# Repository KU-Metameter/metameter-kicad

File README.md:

Bluetooth Multimeter Senior Design Project  
Contains KiCad files

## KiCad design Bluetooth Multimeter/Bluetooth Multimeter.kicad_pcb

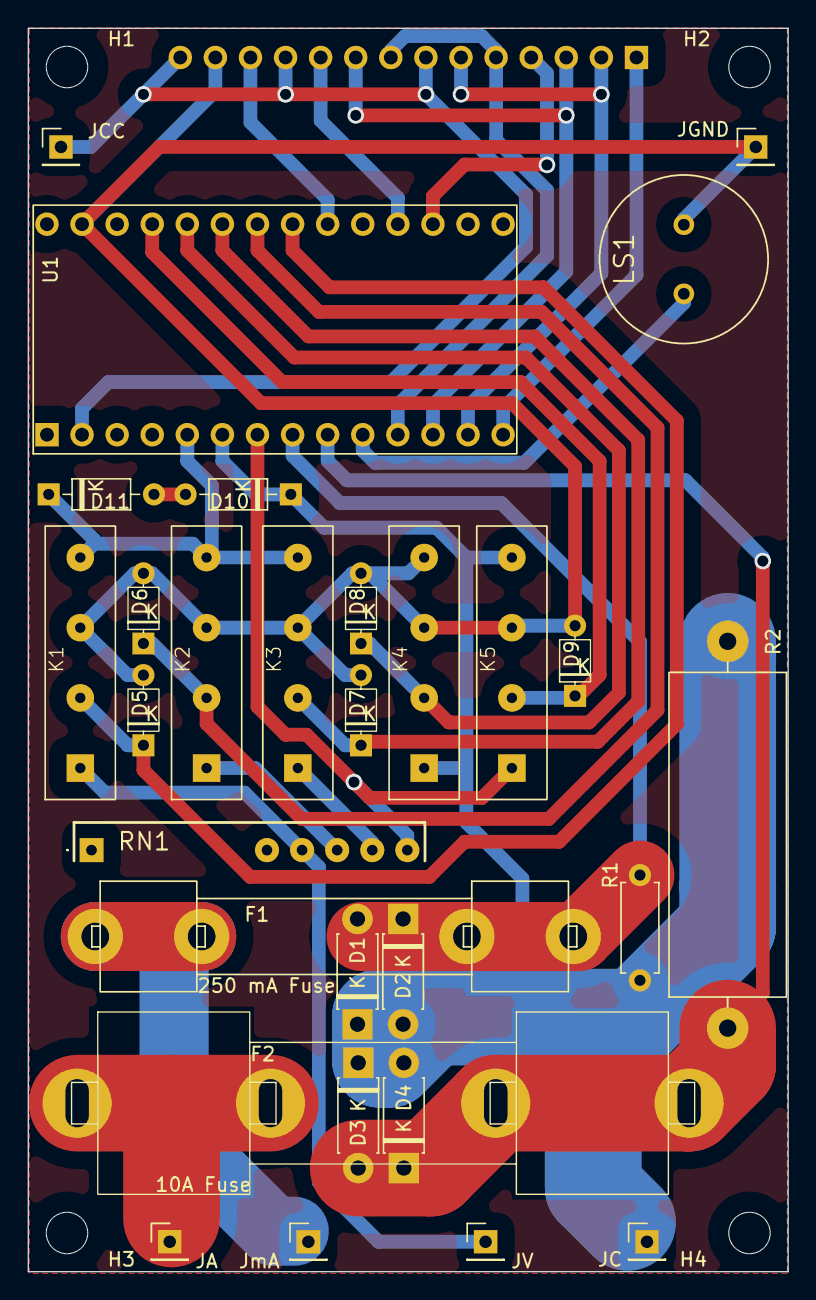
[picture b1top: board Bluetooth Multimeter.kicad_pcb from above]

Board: 2 copper layers, 55.0 x 90.0 mm, 34 parts (1 on the bottom side), 26 nets.

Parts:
D1, D2, D3, D4: 1N4001; D_DO-41_SOD81_P7.62mm_Horizontal
D5, D6, D7, D8, D9: 1N4148; D_DO-35_SOD27_P5.08mm_Horizontal
D10, D11: D_Zener; D_DO-35_SOD27_P7.62mm_Horizontal
DS1: TFT_Interface; PinHeader_1x14_P2.54mm_Vertical_H1.0
F1: 250mA Fuse; LF124061_4
F2: 10A Fuse; LF124041_7
H1, H2, H3, H4: MountingHole; MountingHole_3mm
JA: A; PinHeader_1x01_P2.54mm_Vertical_H0.9mm
JC: Com; PinHeader_1x01_P2.54mm_Vertical_H0.9mm
JCC: 3.3V; PinHeader_1x01_P2.54mm_Vertical_H0.9mm
JGND: GND; PinHeader_1x01_P2.54mm_Vertical_H0.9mm
JV: V/Ohm; PinHeader_1x01_P2.54mm_Vertical_H0.9mm
JmA: mA; PinHeader_1x01_P2.54mm_Vertical_H0.9mm
K1: Low Range; SIL03-1A72-71_4
K2: Medium Range; SIL03-1A72-71_4
K3: High Range; SIL03-1A72-71_4
K4: Ohm Gnd; SIL03-1A72-71_4
K5: V/Ohm Switch; SIL03-1A72-71_4
LS1: PS1240P02BT; XDCR_PS1240P02BT
R1: 5 Ohm; R_Axial_DIN0207_L6.3mm_D2.5mm_P7.62mm_Horizontal
R2: 0.05 Ohm; LOB-1528272_3
RN1: 1776-C68; 1776-C68-1
U1: ItsyBitsy_NRF52840_Big; ItsyBitsy

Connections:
+3.3V: DS1.7 (LED), DS1.11 (RESET), DS1.14 (VCC), JCC.1, U1.2 (3.3V)
/A ADC In: D3.2 (A), D4.1 (K), F2.3, F2.4, R2.1, U1.9 (A4/18)
/A In: F2.1, F2.2, JA.1
/High Range Control: D7.1 (K), K3.3 (K), U1.23 (D11/11)
/Input Common: D1.1 (K), D2.2 (A), D3.1 (K), D4.2 (A), D10.1 (K), JC.1, K4.1 (COM), K5.7 (NO), R1.1, R2.2, U1.6 (A1/15)
/Low Range Control: D5.1 (K), K1.3 (K), U1.21 (D9/9)
/MISO: DS1.2 (T_DO(MISO)), DS1.6 (SDO(MISO)), U1.13 (MISO/23)
/MOSI: DS1.3 (T_DIN(MOSI)), DS1.9 (SDI(MOSI)), U1.12 (MOSI/24)
/Med Range Control: D6.1 (K), K2.3 (K), U1.22 (D10/10)
/Ohm Gnd Control: D8.1 (K), K4.3 (K), U1.24 (D12/12)
/Ohm Vout: K5.1 (COM), RN1.6 (COM), U1.7 (A2/16)
/SCK: DS1.5 (T_CLK(SCK)), DS1.8 (SCK), U1.11 (SCK/25)
/Speaker Control: LS1.1, U1.10 (A5/19)
/TFT CS: DS1.12 (CS), U1.20 (D7/7)
/TFT DC: DS1.10 (DC), U1.18 (SCL/22)
/TOUCH CS: DS1.4 (T_CS), U1.17 (SDA/21)
/TOUCH IRQ: DS1.1 (T_IRQ), U1.14 (D2/2)
/V/Ohm ADC In: D11.1 (K), K1.7 (NO), K2.7 (NO), K3.7 (NO), U1.5 (A0/14)
/V/Ohm Control: D9.1 (K), K5.3 (K), U1.25 (D13/13)
/V/Ohm In: JV.1, K1.1 (COM), RN1.3 (90k)
/mA ADC In: D1.2 (A), D2.1 (K), F1.3, F1.4, R1.2, U1.8 (A3/17)
/mA In: F1.1, F1.2, JmA.1
GND: D5.2 (A), D6.2 (A), D7.2 (A), D8.2 (A), D9.2 (A), DS1.13 (GND), JGND.1, K1.5 (A), K2.5 (A), K3.5 (A), K4.5 (A), K4.7 (NO), K5.5 (A), LS1.2, U1.27 (GND)
unnamed: D10.2 (A), D11.2 (A)
unnamed: K2.1 (COM), RN1.4 (9k)
unnamed: K3.1 (COM), RN1.5 (1k)

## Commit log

2023-03-21 initial commit fix
2023-03-21 fixed itsybitsy footprint and lcd connection
2023-03-21 added readme and license
2023-03-22 pcb modifications based on first shop board
2023-03-22 finalized rev 2 board to be milled
2023-03-24 began work on inverted screen connect project
2023-03-26 made inverted connector PCB main project, fixed ohmeter
2023-04-04 rerouted board for external fab
2023-04-10 finalized (fingers crossed) PCB and Schematic
